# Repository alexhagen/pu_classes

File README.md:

# pu_classes
classwork from my time at Purdue University

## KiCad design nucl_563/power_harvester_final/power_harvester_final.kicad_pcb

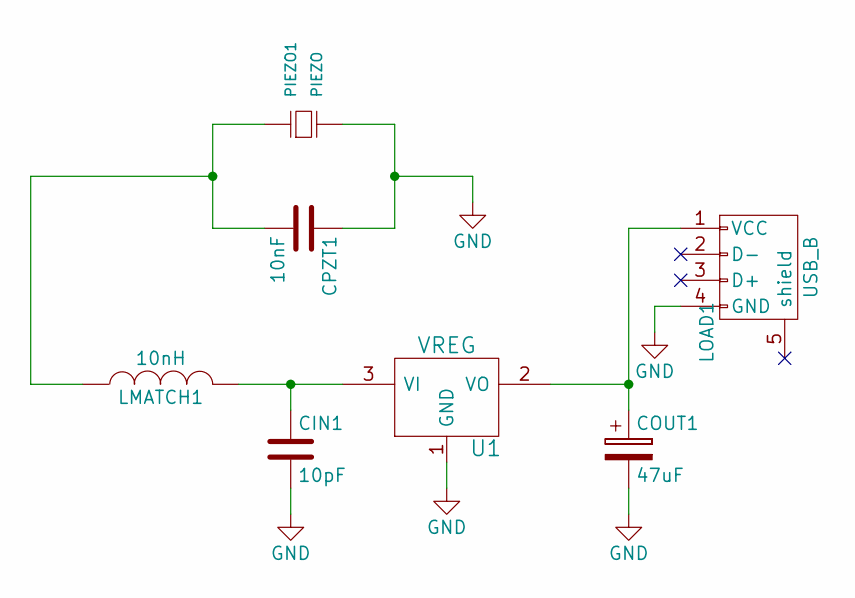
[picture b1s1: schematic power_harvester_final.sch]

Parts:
CIN1: 10pF; C_0402
COUT1: 47uF; c_elec_4x4.5
CPZT1: 10nF; C_0402
LMATCH1: 10nH; C_0402
LOAD1: USB_B; USB_Micro-B
PIEZO1: PIEZO; PZT
U1: VREG

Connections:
GND: CIN1.2, COUT1.2, CPZT1.1, LOAD1.4 (GND), PIEZO1.2, U1.1 (GND)
unnamed: CIN1.1, LMATCH1.2, U1.3 (VI)
unnamed: COUT1.1, LOAD1.1 (VCC), U1.2 (VO)
unnamed: CPZT1.2, LMATCH1.1, PIEZO1.1

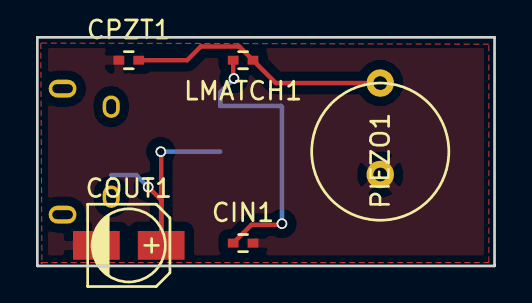
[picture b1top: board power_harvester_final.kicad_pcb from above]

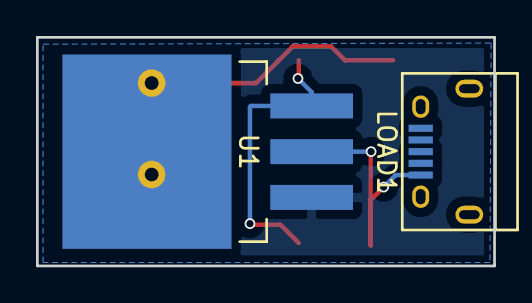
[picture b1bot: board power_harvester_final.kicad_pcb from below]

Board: 2 copper layers, 25.4 x 12.7 mm, 7 parts (2 on the bottom side), 4 nets.

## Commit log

2017-05-14 added 563 stuff
2017-05-14 added nucl_697
2017-05-14 added phys 556
2017-05-14 added me513
2017-05-14 added cs530
2017-05-14 added aae550
